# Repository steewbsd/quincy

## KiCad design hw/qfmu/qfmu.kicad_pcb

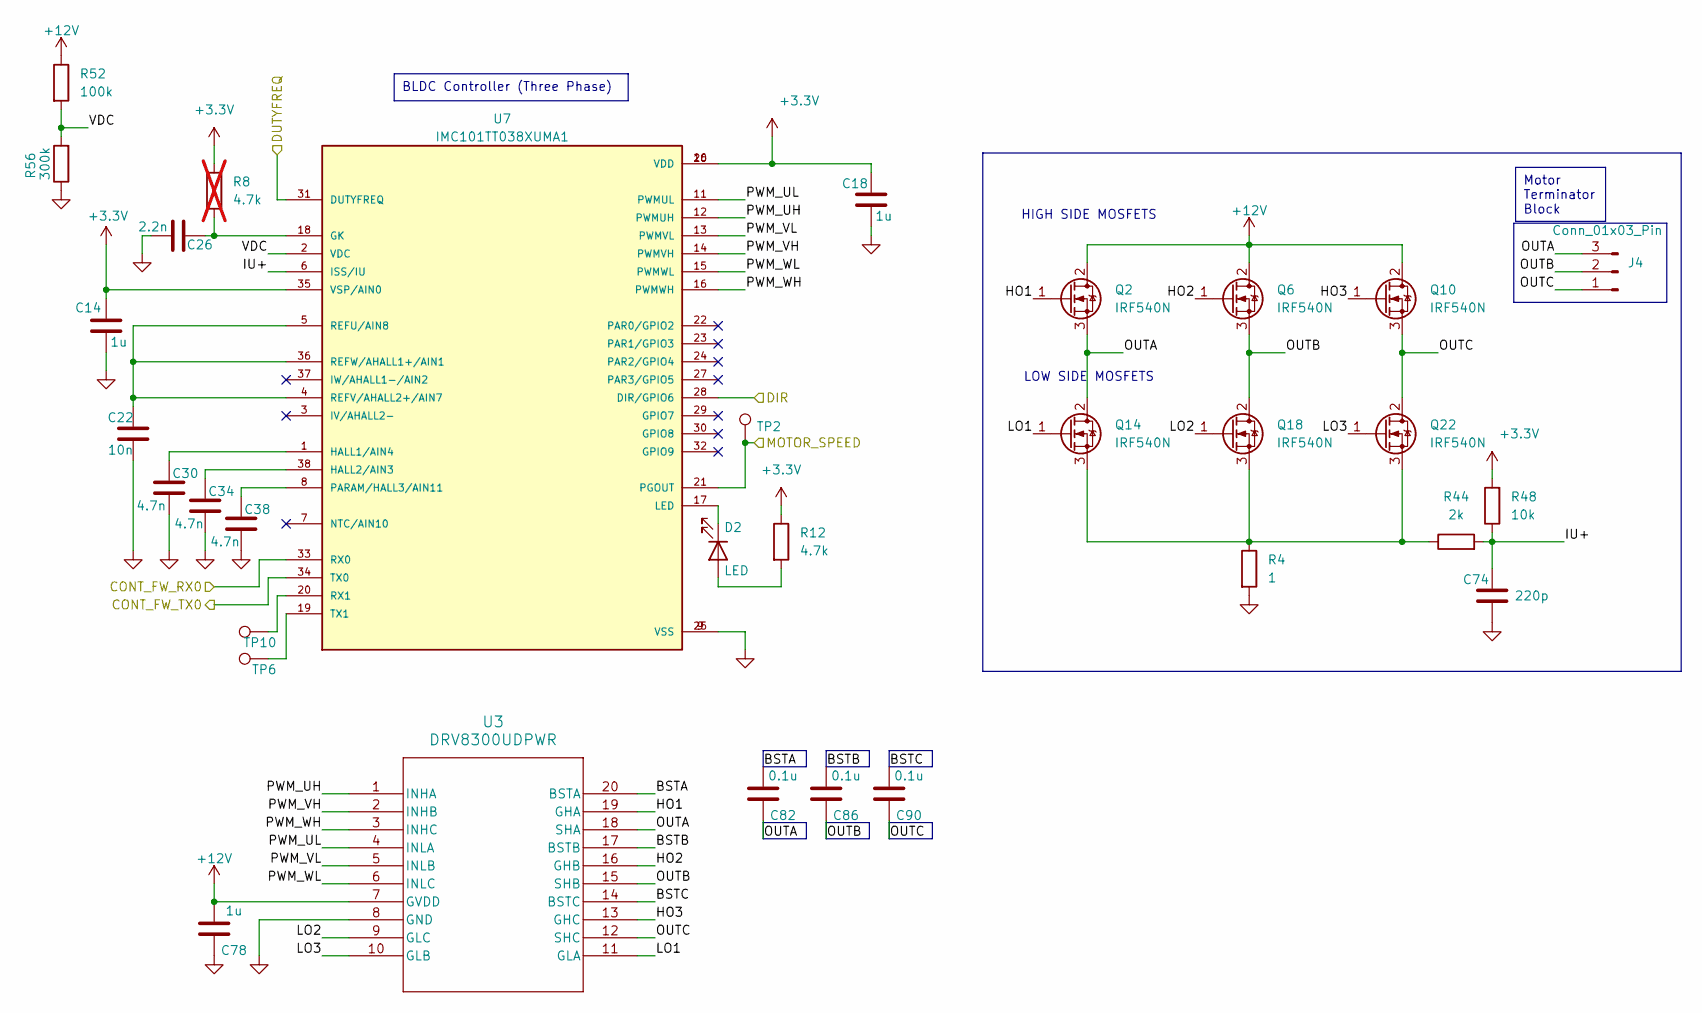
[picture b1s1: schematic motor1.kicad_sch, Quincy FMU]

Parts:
C14, C18, C78: 1u; C_0805_2012Metric_Pad1.18x1.45mm_HandSolder
C22: 10n; C_0805_2012Metric_Pad1.18x1.45mm_HandSolder
C26: 2.2n; C_0805_2012Metric_Pad1.18x1.45mm_HandSolder
C30, C34, C38: 4.7n; C_0805_2012Metric_Pad1.18x1.45mm_HandSolder
C74: 220p; C_0805_2012Metric_Pad1.18x1.45mm_HandSolder
C82, C86, C90: 0.1u; C_0805_2012Metric_Pad1.18x1.45mm_HandSolder
D2: LED; LED_1206_3216Metric_Pad1.42x1.75mm_HandSolder
J4: Conn_01x03_Pin; PhoenixContact_SPT_1.5_3-H-3.5_1x03_P3.5mm_Horizontal
Q2, Q6, Q10, Q14, Q18, Q22: IRF540N; TO-220-3_Horizontal_TabDown
R4: 1; R_0805_2012Metric_Pad1.20x1.40mm_HandSolder
R8: 4.7k; R_0805_2012Metric_Pad1.20x1.40mm_HandSolder; not fitted
R12: 4.7k; R_0805_2012Metric_Pad1.20x1.40mm_HandSolder
R44: 2k; R_0805_2012Metric_Pad1.20x1.40mm_HandSolder
R48: 10k; R_0805_2012Metric_Pad1.20x1.40mm_HandSolder
R52: 100k; R_0805_2012Metric_Pad1.20x1.40mm_HandSolder
R56: 300k; R_0805_2012Metric_Pad1.20x1.40mm_HandSolder
TP2, TP6, TP10: TestPoint; Pin_D0.7mm_L6.5mm_W1.8mm_FlatFork
U3: DRV8300UDPWR; TSSOP_0DIPWR_TEX
U7: IMC101TT038XUMA1; SOP50P640X110-38N; PARTREV 1.6

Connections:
+3.3V: C14.1, C18.1, R8.1, R12.1, R48.2, U7.10 (VDD), U7.26 (VDD), U7.35 (VSP/AIN0); also elsewhere on the board
+12V: C78.2, Q2.2 (D), Q6.2 (D), Q10.2 (D), R52.1, U3.7 (GVDD); also elsewhere on the board
/Microcontroller/CONT_FW_RX0_2: U7.33 (RX0); also elsewhere on the board
/Microcontroller/CONT_FW_TX0_2: U7.34 (TX0); also elsewhere on the board
/Microcontroller/DIR2: U7.28 (DIR/GPIO6); also elsewhere on the board
/Microcontroller/DUTY2: U7.31 (DUTYFREQ); also elsewhere on the board
/Microcontroller/MOTOR_SPEED2: TP2.1, U7.21 (PGOUT); also elsewhere on the board
/Motor 2/BSTA: C82.2, U3.20 (BSTA)
/Motor 2/BSTB: C86.2, U3.17 (BSTB)
/Motor 2/BSTC: C90.2, U3.14 (BSTC)
/Motor 2/HO1: Q2.1 (G), U3.19 (GHA)
/Motor 2/HO2: Q6.1 (G), U3.16 (GHB)
/Motor 2/HO3: Q10.1 (G), U3.13 (GHC)
/Motor 2/IU+: C74.1, R44.2, R48.1, U7.6 (ISS/IU)
/Motor 2/LO1: Q14.1 (G), U3.11 (GLA)
/Motor 2/LO2: Q18.1 (G), U3.9 (GLC)
/Motor 2/LO3: Q22.1 (G), U3.10 (GLB)
/Motor 2/OUTA: C82.1, J4.3, Q2.3 (S), Q14.2 (D), U3.18 (SHA)
/Motor 2/OUTB: C86.1, J4.2, Q6.3 (S), Q18.2 (D), U3.15 (SHB)
/Motor 2/OUTC: C90.1, J4.1, Q10.3 (S), Q22.2 (D), U3.12 (SHC)
/Motor 2/PWM_UH: U3.1 (INHA), U7.12 (PWMUH)
/Motor 2/PWM_UL: U3.4 (INLA), U7.11 (PWMUL)
/Motor 2/PWM_VH: U3.2 (INHB), U7.14 (PWMVH)
/Motor 2/PWM_VL: U3.5 (INLB), U7.13 (PWMVL)
/Motor 2/PWM_WH: U3.3 (INHC), U7.16 (PWMWH)
/Motor 2/PWM_WL: U3.6 (INLC), U7.15 (PWMWL)
/Motor 2/VDC: R52.2, R56.2, U7.2 (VDC)
GND: C14.2, C18.2, C22.2, C26.1, C30.2, C34.2, C38.2, C74.2, C78.1, R4.2, R56.1, U3.8 (GND), U7.9 (VSS), U7.25 (VSS); also elsewhere on the board
unnamed: D2.2 (A), R12.2
unnamed: D2.1 (K), U7.17 (LED)
unnamed: Q14.3 (S), Q18.3 (S), Q22.3 (S), R4.1, R44.1
unnamed: C26.2, R8.2, U7.18 (GK)
unnamed: C30.1, U7.1 (HALL1/AIN4)
unnamed: C34.1, U7.38 (HALL2/AIN3)
unnamed: C38.1, U7.8 (PARAM/HALL3/AIN11)
unnamed: C22.1, U7.4 (REFV/AHALL2+/AIN7), U7.5 (REFU/AIN8), U7.36 (REFW/AHALL1+/AIN1)
unnamed: TP10.1, U7.20 (RX1)
unnamed: TP6.1, U7.19 (TX1)

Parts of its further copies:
C13, C15, C16, C17, C19, C20, C77, C79, C80: 1u; C_0805_2012Metric_Pad1.18x1.45mm_HandSolder
C21, C23, C24: 10n; C_0805_2012Metric_Pad1.18x1.45mm_HandSolder
C25, C27, C28: 2.2n; C_0805_2012Metric_Pad1.18x1.45mm_HandSolder
C29, C31, C32, C33, C35, C36, C37, C39, C40: 4.7n; C_0805_2012Metric_Pad1.18x1.45mm_HandSolder
C73, C75, C76: 220p; C_0805_2012Metric_Pad1.18x1.45mm_HandSolder
C81, C83, C84, C85, C87, C88, C89, C91, C92: 0.1u; C_0805_2012Metric_Pad1.18x1.45mm_HandSolder
D1, D3, D4: LED; LED_1206_3216Metric_Pad1.42x1.75mm_HandSolder
J3, J5, J6: Conn_01x03_Pin; PhoenixContact_SPT_1.5_3-H-3.5_1x03_P3.5mm_Horizontal
Q1, Q3, Q4, Q5, Q7, Q8, Q9, Q11, Q12, Q13, Q15, Q16, Q17, Q19, Q20, Q21, Q23, Q24: IRF540N; TO-220-3_Horizontal_TabDown
R2, R41, R42: 1; R_0805_2012Metric_Pad1.20x1.40mm_HandSolder
R7, R9, R10: 4.7k; R_0805_2012Metric_Pad1.20x1.40mm_HandSolder; not fitted
R11, R13, R14: 4.7k; R_0805_2012Metric_Pad1.20x1.40mm_HandSolder
R43, R45, R46: 2k; R_0805_2012Metric_Pad1.20x1.40mm_HandSolder
R47, R49, R50: 10k; R_0805_2012Metric_Pad1.20x1.40mm_HandSolder
R51, R53, R54: 100k; R_0805_2012Metric_Pad1.20x1.40mm_HandSolder
R55, R57, R58: 300k; R_0805_2012Metric_Pad1.20x1.40mm_HandSolder
TP1, TP3, TP4, TP5, TP7, TP8, TP9, TP11, TP12: TestPoint; Pin_D0.7mm_L6.5mm_W1.8mm_FlatFork
U2, U4, U5: DRV8300UDPWR; TSSOP_0DIPWR_TEX
U6, U8, U9: IMC101TT038XUMA1; SOP50P640X110-38N; PARTREV 1.6

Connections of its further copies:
+3.3V: C13.1, C15.1, C16.1, C17.1, C19.1, C20.1, R7.1, R9.1, R10.1, R11.1, R13.1, R14.1, R47.2, R49.2, R50.2, U6.10 (VDD), U6.26 (VDD), U6.35 (VSP/AIN0), U8.10 (VDD), U8.26 (VDD), U8.35 (VSP/AIN0), U9.10 (VDD), U9.26 (VDD), U9.35 (VSP/AIN0); also elsewhere on the board
+12V: C77.2, C79.2, C80.2, Q1.2 (D), Q3.2 (D), Q4.2 (D), Q5.2 (D), Q7.2 (D), Q8.2 (D), Q9.2 (D), Q11.2 (D), Q12.2 (D), R51.1, R53.1, R54.1, U2.7 (GVDD), U4.7 (GVDD), U5.7 (GVDD); also elsewhere on the board
/Microcontroller/CONT_FW_RX0_1: U6.33 (RX0); also elsewhere on the board
/Microcontroller/CONT_FW_RX0_3: U8.33 (RX0); also elsewhere on the board
/Microcontroller/CONT_FW_RX0_4: U9.33 (RX0); also elsewhere on the board
/Microcontroller/CONT_FW_TX0_1: U6.34 (TX0); also elsewhere on the board
/Microcontroller/CONT_FW_TX0_3: U8.34 (TX0); also elsewhere on the board
/Microcontroller/CONT_FW_TX0_4: U9.34 (TX0); also elsewhere on the board
/Microcontroller/DIR1: U6.28 (DIR/GPIO6); also elsewhere on the board
/Microcontroller/DIR3: U8.28 (DIR/GPIO6); also elsewhere on the board
/Microcontroller/DIR4: U9.28 (DIR/GPIO6); also elsewhere on the board
/Microcontroller/DUTY1: U6.31 (DUTYFREQ); also elsewhere on the board
/Microcontroller/DUTY3: U8.31 (DUTYFREQ); also elsewhere on the board
/Microcontroller/DUTY4: U9.31 (DUTYFREQ); also elsewhere on the board
/Microcontroller/MOTOR_SPEED1: TP1.1, U6.21 (PGOUT); also elsewhere on the board
/Microcontroller/MOTOR_SPEED3: TP3.1, U8.21 (PGOUT); also elsewhere on the board
/Microcontroller/MOTOR_SPEED4: TP4.1, U9.21 (PGOUT); also elsewhere on the board
/Motor 1/BSTA: C81.2, U2.20 (BSTA)
/Motor 1/BSTB: C85.2, U2.17 (BSTB)
/Motor 1/BSTC: C89.2, U2.14 (BSTC)
/Motor 1/HO1: Q1.1 (G), U2.19 (GHA)
/Motor 1/HO2: Q5.1 (G), U2.16 (GHB)
/Motor 1/HO3: Q9.1 (G), U2.13 (GHC)
/Motor 1/IU+: C73.1, R43.2, R47.1, U6.6 (ISS/IU)
/Motor 1/LO1: Q13.1 (G), U2.11 (GLA)
/Motor 1/LO2: Q17.1 (G), U2.9 (GLC)
/Motor 1/LO3: Q21.1 (G), U2.10 (GLB)
/Motor 1/OUTA: C81.1, J3.3, Q1.3 (S), Q13.2 (D), U2.18 (SHA)
/Motor 1/OUTB: C85.1, J3.2, Q5.3 (S), Q17.2 (D), U2.15 (SHB)
/Motor 1/OUTC: C89.1, J3.1, Q9.3 (S), Q21.2 (D), U2.12 (SHC)
/Motor 1/PWM_UH: U2.1 (INHA), U6.12 (PWMUH)
/Motor 1/PWM_UL: U2.4 (INLA), U6.11 (PWMUL)
/Motor 1/PWM_VH: U2.2 (INHB), U6.14 (PWMVH)
/Motor 1/PWM_VL: U2.5 (INLB), U6.13 (PWMVL)
/Motor 1/PWM_WH: U2.3 (INHC), U6.16 (PWMWH)
/Motor 1/PWM_WL: U2.6 (INLC), U6.15 (PWMWL)
/Motor 1/VDC: R51.2, R55.2, U6.2 (VDC)
/Motor 3/BSTA: C83.2, U4.20 (BSTA)
/Motor 3/BSTB: C87.2, U4.17 (BSTB)
/Motor 3/BSTC: C91.2, U4.14 (BSTC)
/Motor 3/HO1: Q3.1 (G), U4.19 (GHA)
/Motor 3/HO2: Q7.1 (G), U4.16 (GHB)
/Motor 3/HO3: Q11.1 (G), U4.13 (GHC)
/Motor 3/IU+: C75.1, R45.2, R49.1, U8.6 (ISS/IU)
/Motor 3/LO1: Q15.1 (G), U4.11 (GLA)
/Motor 3/LO2: Q19.1 (G), U4.9 (GLC)
/Motor 3/LO3: Q23.1 (G), U4.10 (GLB)
/Motor 3/OUTA: C83.1, J5.3, Q3.3 (S), Q15.2 (D), U4.18 (SHA)
/Motor 3/OUTB: C87.1, J5.2, Q7.3 (S), Q19.2 (D), U4.15 (SHB)
/Motor 3/OUTC: C91.1, J5.1, Q11.3 (S), Q23.2 (D), U4.12 (SHC)
/Motor 3/PWM_UH: U4.1 (INHA), U8.12 (PWMUH)
/Motor 3/PWM_UL: U4.4 (INLA), U8.11 (PWMUL)
/Motor 3/PWM_VH: U4.2 (INHB), U8.14 (PWMVH)
/Motor 3/PWM_VL: U4.5 (INLB), U8.13 (PWMVL)
/Motor 3/PWM_WH: U4.3 (INHC), U8.16 (PWMWH)
/Motor 3/PWM_WL: U4.6 (INLC), U8.15 (PWMWL)
/Motor 3/VDC: R53.2, R57.2, U8.2 (VDC)
/Motor 4/BSTA: C84.2, U5.20 (BSTA)
/Motor 4/BSTB: C88.2, U5.17 (BSTB)
/Motor 4/BSTC: C92.2, U5.14 (BSTC)
/Motor 4/HO1: Q4.1 (G), U5.19 (GHA)
/Motor 4/HO2: Q8.1 (G), U5.16 (GHB)
/Motor 4/HO3: Q12.1 (G), U5.13 (GHC)
/Motor 4/IU+: C76.1, R46.2, R50.1, U9.6 (ISS/IU)
/Motor 4/LO1: Q16.1 (G), U5.11 (GLA)
/Motor 4/LO2: Q20.1 (G), U5.9 (GLC)
/Motor 4/LO3: Q24.1 (G), U5.10 (GLB)
/Motor 4/OUTA: C84.1, J6.3, Q4.3 (S), Q16.2 (D), U5.18 (SHA)
/Motor 4/OUTB: C88.1, J6.2, Q8.3 (S), Q20.2 (D), U5.15 (SHB)
/Motor 4/OUTC: C92.1, J6.1, Q12.3 (S), Q24.2 (D), U5.12 (SHC)
/Motor 4/PWM_UH: U5.1 (INHA), U9.12 (PWMUH)
/Motor 4/PWM_UL: U5.4 (INLA), U9.11 (PWMUL)
/Motor 4/PWM_VH: U5.2 (INHB), U9.14 (PWMVH)
/Motor 4/PWM_VL: U5.5 (INLB), U9.13 (PWMVL)
/Motor 4/PWM_WH: U5.3 (INHC), U9.16 (PWMWH)
/Motor 4/PWM_WL: U5.6 (INLC), U9.15 (PWMWL)
/Motor 4/VDC: R54.2, R58.2, U9.2 (VDC)
GND: C13.2, C15.2, C16.2, C17.2, C19.2, C20.2, C21.2, C23.2, C24.2, C25.1, C27.1, C28.1, C29.2, C31.2, C32.2, C33.2, C35.2, C36.2, C37.2, C39.2, C40.2, C73.2, C75.2, C76.2, C77.1, C79.1, C80.1, R2.2, R41.2, R42.2, R55.1, R57.1, R58.1, U2.8 (GND), U4.8 (GND), U5.8 (GND), U6.9 (VSS), U6.25 (VSS), U8.9 (VSS), U8.25 (VSS), U9.9 (VSS), U9.25 (VSS); also elsewhere on the board
unnamed: D1.2 (A), R11.2
unnamed: D1.1 (K), U6.17 (LED)
unnamed: D3.2 (A), R13.2
unnamed: D3.1 (K), U8.17 (LED)
unnamed: D4.2 (A), R14.2
unnamed: D4.1 (K), U9.17 (LED)
unnamed: Q13.3 (S), Q17.3 (S), Q21.3 (S), R2.1, R43.1
unnamed: Q15.3 (S), Q19.3 (S), Q23.3 (S), R41.1, R45.1
unnamed: Q16.3 (S), Q20.3 (S), Q24.3 (S), R42.1, R46.1
unnamed: C25.2, R7.2, U6.18 (GK)
unnamed: C29.1, U6.1 (HALL1/AIN4)
unnamed: C33.1, U6.38 (HALL2/AIN3)
unnamed: C37.1, U6.8 (PARAM/HALL3/AIN11)
unnamed: C21.1, U6.4 (REFV/AHALL2+/AIN7), U6.5 (REFU/AIN8), U6.36 (REFW/AHALL1+/AIN1)
unnamed: TP9.1, U6.20 (RX1)
unnamed: TP5.1, U6.19 (TX1)
unnamed: C27.2, R9.2, U8.18 (GK)
unnamed: C31.1, U8.1 (HALL1/AIN4)
unnamed: C35.1, U8.38 (HALL2/AIN3)
unnamed: C39.1, U8.8 (PARAM/HALL3/AIN11)
unnamed: C23.1, U8.4 (REFV/AHALL2+/AIN7), U8.5 (REFU/AIN8), U8.36 (REFW/AHALL1+/AIN1)
unnamed: TP11.1, U8.20 (RX1)
unnamed: TP7.1, U8.19 (TX1)
unnamed: C28.2, R10.2, U9.18 (GK)
unnamed: C32.1, U9.1 (HALL1/AIN4)
unnamed: C36.1, U9.38 (HALL2/AIN3)
unnamed: C40.1, U9.8 (PARAM/HALL3/AIN11)
unnamed: C24.1, U9.4 (REFV/AHALL2+/AIN7), U9.5 (REFU/AIN8), U9.36 (REFW/AHALL1+/AIN1)
unnamed: TP12.1, U9.20 (RX1)
unnamed: TP8.1, U9.19 (TX1)

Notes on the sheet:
Motor Terminator Block
BLDC Controller (Three Phase)
HIGH SIDE MOSFETS
LOW SIDE MOSFETS

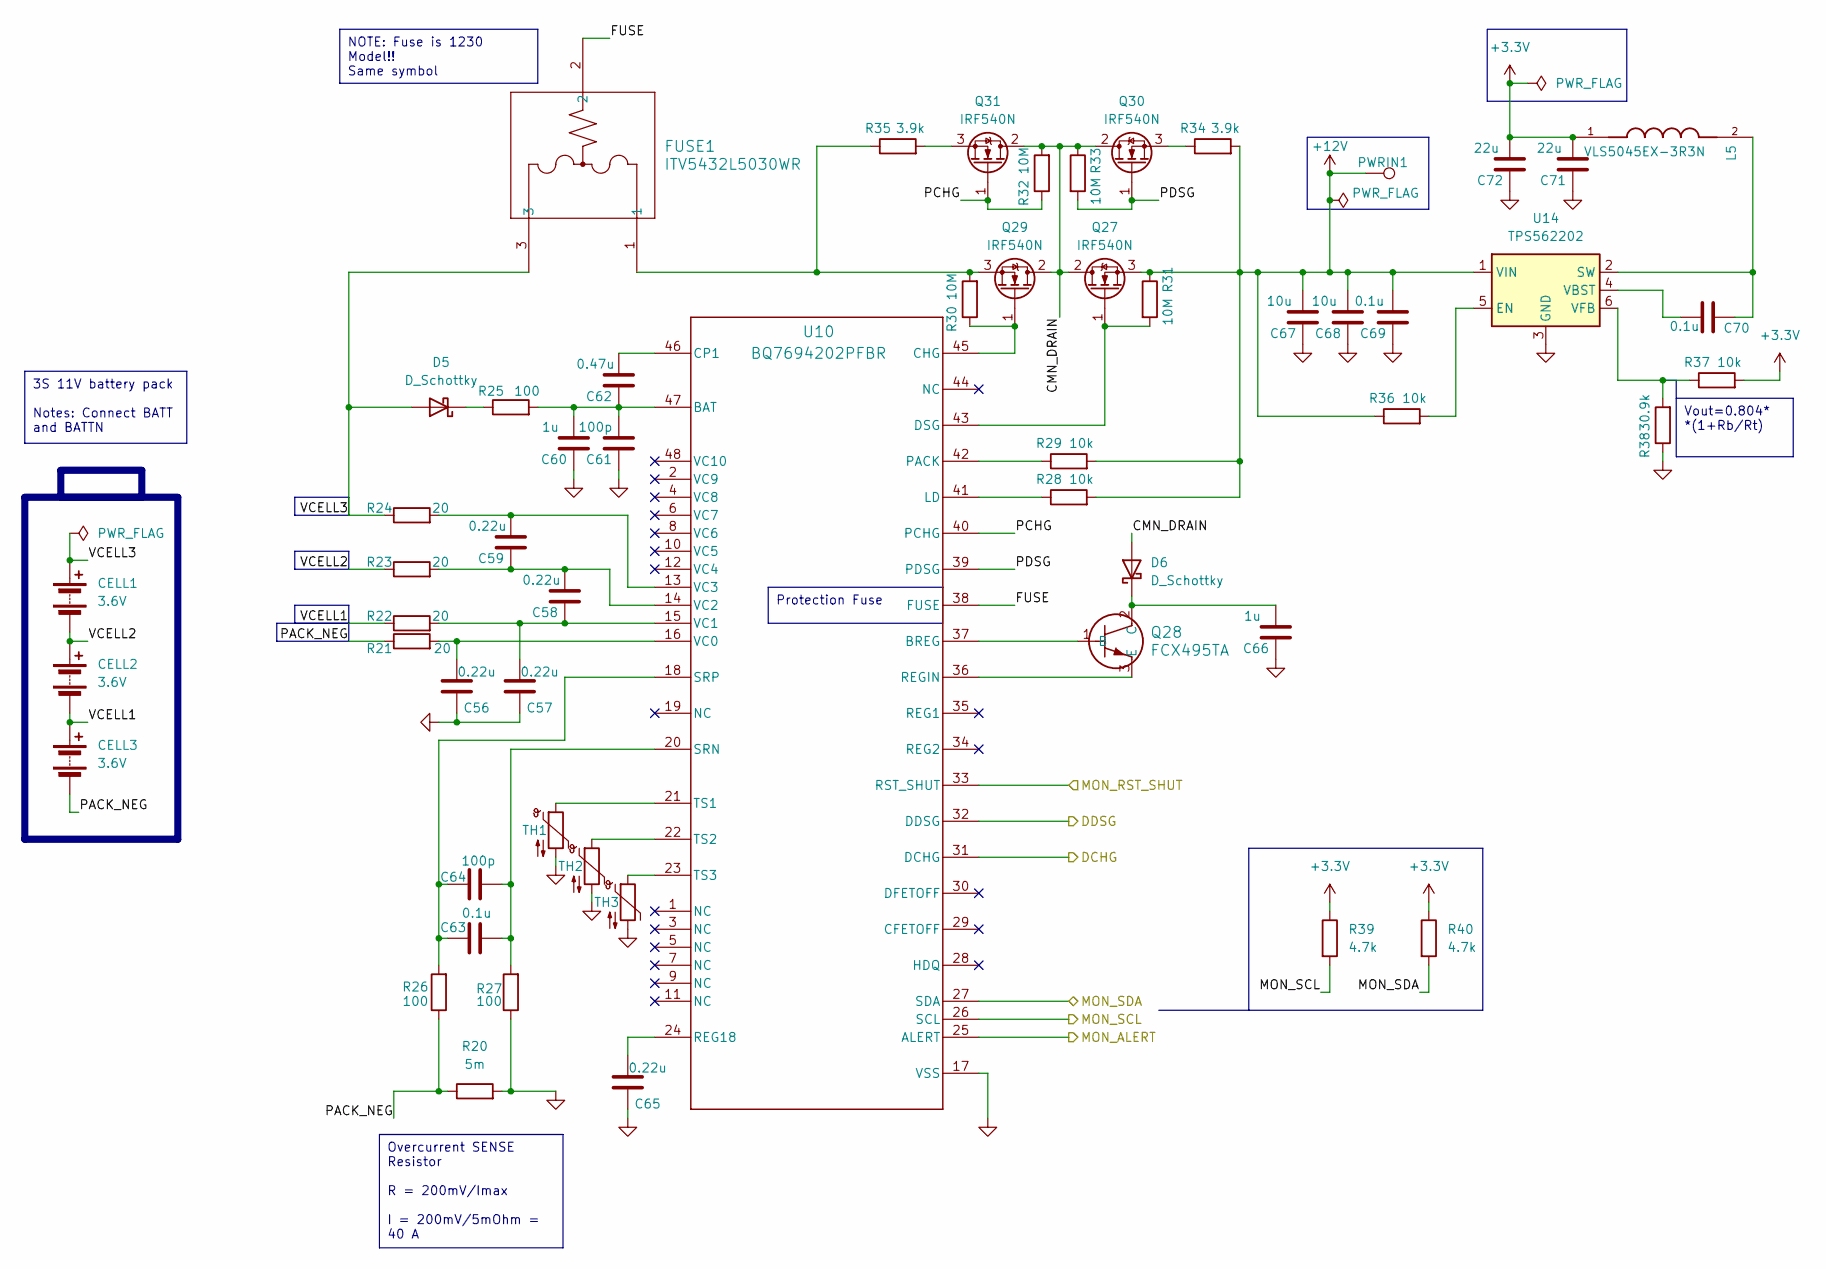
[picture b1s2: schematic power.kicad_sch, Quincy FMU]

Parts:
C56, C57, C58, C59, C65: 0.22u; C_0805_2012Metric_Pad1.18x1.45mm_HandSolder
C60, C66: 1u; C_0805_2012Metric_Pad1.18x1.45mm_HandSolder
C61, C64: 100p; C_0805_2012Metric_Pad1.18x1.45mm_HandSolder
C62: 0.47u; C_0805_2012Metric_Pad1.18x1.45mm_HandSolder
C63, C69, C70: 0.1u; C_0805_2012Metric_Pad1.18x1.45mm_HandSolder
C67, C68: 10u; C_0805_2012Metric_Pad1.18x1.45mm_HandSolder
C71, C72: 22u; C_0805_2012Metric_Pad1.18x1.45mm_HandSolder
CELL1, CELL2, CELL3: 3.6V
D5, D6: D_Schottky; D_SOD-123
FUSE1: ITV5432L5030WR; QFN4_ITV5432_LTF
L5: VLS5045EX-3R3N; IND_VLS5045EX-3R3N; PARTREV N/A
PWRIN1: TestPoint; Pin_D0.7mm_L6.5mm_W1.8mm_FlatFork
Q27, Q29, Q30, Q31: IRF540N; TO-220-3_Horizontal_TabDown
Q28: FCX495TA; SOT89_DIO
R20: 5m; R_2512_6332Metric_Pad1.40x3.35mm_HandSolder
R21, R22, R23, R24: 20; R_0805_2012Metric_Pad1.20x1.40mm_HandSolder
R25, R26, R27: 100; R_0805_2012Metric_Pad1.20x1.40mm_HandSolder
R28, R29, R36, R37: 10k; R_0805_2012Metric_Pad1.20x1.40mm_HandSolder
R30, R31, R32, R33: 10M; R_0805_2012Metric_Pad1.20x1.40mm_HandSolder
R34, R35: 3.9k; R_0805_2012Metric_Pad1.20x1.40mm_HandSolder
R38: 30.9k; R_0805_2012Metric_Pad1.20x1.40mm_HandSolder
R39, R40: 4.7k; R_0805_2012Metric_Pad1.20x1.40mm_HandSolder
TH1, TH2, TH3: Thermistor_NTC; R_0603_1608Metric_Pad0.98x0.95mm_HandSolder
U10: BQ7694202PFBR; PFB0048A_N
U14: TPS562202; SOT-563

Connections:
+3.3V: C71.2, C72.2, L5.1, R37.2, R39.1, R40.1; also elsewhere on the board
+12V: C67.2, C68.2, C69.2, PWRIN1.1, Q27.3 (S), R28.2, R29.2, R31.1, R34.2, R36.1, U14.1 (VIN); also elsewhere on the board
/Microcontroller/DCHG: U10.31 (DCHG); also elsewhere on the board
/Microcontroller/DDSG: U10.32 (DDSG); also elsewhere on the board
/Microcontroller/MON_ALERT: U10.25 (ALERT); also elsewhere on the board
/Microcontroller/MON_RST_SHUT: U10.33 (RST_SHUT); also elsewhere on the board
/Power/CMN_DRAIN: D6.2 (A), Q27.2 (D), Q29.2 (D), Q30.2 (D), Q31.2 (D), R32.2, R33.1
/Power/FUSE: FUSE1.2, U10.38 (FUSE)
/Power/MON_SCL: R39.2, U10.26 (SCL); also elsewhere on the board
/Power/MON_SDA: R40.2, U10.27 (SDA); also elsewhere on the board
/Power/PACK_NEG: CELL3.2 (-), R20.1, R21.1, R26.1
/Power/PCHG: Q31.1 (G), R32.1, U10.40 (PCHG)
/Power/PDSG: Q30.1 (G), R33.2, U10.39 (PDSG)
/Power/VCELL1: CELL2.2 (-), CELL3.1 (+), R22.1
/Power/VCELL2: CELL1.2 (-), CELL2.1 (+), R23.1
/Power/VCELL3: CELL1.1 (+), D5.2 (A), FUSE1.3, R24.1
GND: C56.1, C57.1, C60.1, C61.1, C65.1, C66.1, C67.1, C68.1, C69.1, C71.1, C72.1, R20.2, R27.1, R38.1, TH1.2, TH2.2, TH3.2, U10.17 (VSS), U14.3 (GND); also elsewhere on the board
unnamed: D5.1 (K), R25.1
unnamed: C66.2, D6.1 (K), Q28.2 (C)
unnamed: Q27.1 (G), R31.2, U10.43 (DSG)
unnamed: Q28.1 (B), U10.37 (BREG)
unnamed: Q28.3 (E), U10.36 (REGIN)
unnamed: Q29.1 (G), R30.1, U10.45 (CHG)
unnamed: FUSE1.1, Q29.3 (S), R30.2, R35.1
unnamed: Q30.3 (S), R34.1
unnamed: Q31.3 (S), R35.2
unnamed: C60.2, C61.2, C62.1, R25.2, U10.47 (BAT)
unnamed: C62.2, U10.46 (CP1)
unnamed: R28.1, U10.41 (LD)
unnamed: R29.1, U10.42 (PACK)
unnamed: C65.2, U10.24 (REG18)
unnamed: C63.1, C64.1, R27.2, U10.20 (SRN)
unnamed: C63.2, C64.2, R26.2, U10.18 (SRP)
unnamed: TH1.1, U10.21 (TS1)
unnamed: TH2.1, U10.22 (TS2)
unnamed: TH3.1, U10.23 (TS3)
unnamed: C56.2, R21.2, U10.16 (VC0)
unnamed: C57.2, C58.1, R22.2, U10.15 (VC1)
unnamed: C58.2, C59.1, R23.2, U10.14 (VC2)
unnamed: C59.2, R24.2, U10.13 (VC3)
unnamed: R36.2, U14.5 (EN)
unnamed: C70.1, L5.2, U14.2 (SW)
unnamed: C70.2, U14.4 (VBST)
unnamed: R37.1, R38.2, U14.6 (VFB)

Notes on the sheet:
NOTE: Fuse is 1230 Model!! Same symbol
Vout=0.804* *(1+Rb/Rt)
Protection Fuse
Overcurrent SENSE Resistor R = 200mV/Imax I = 200mV/5mOhm = 40 A
3S 11V battery pack Notes: Connect BATT and BATTN

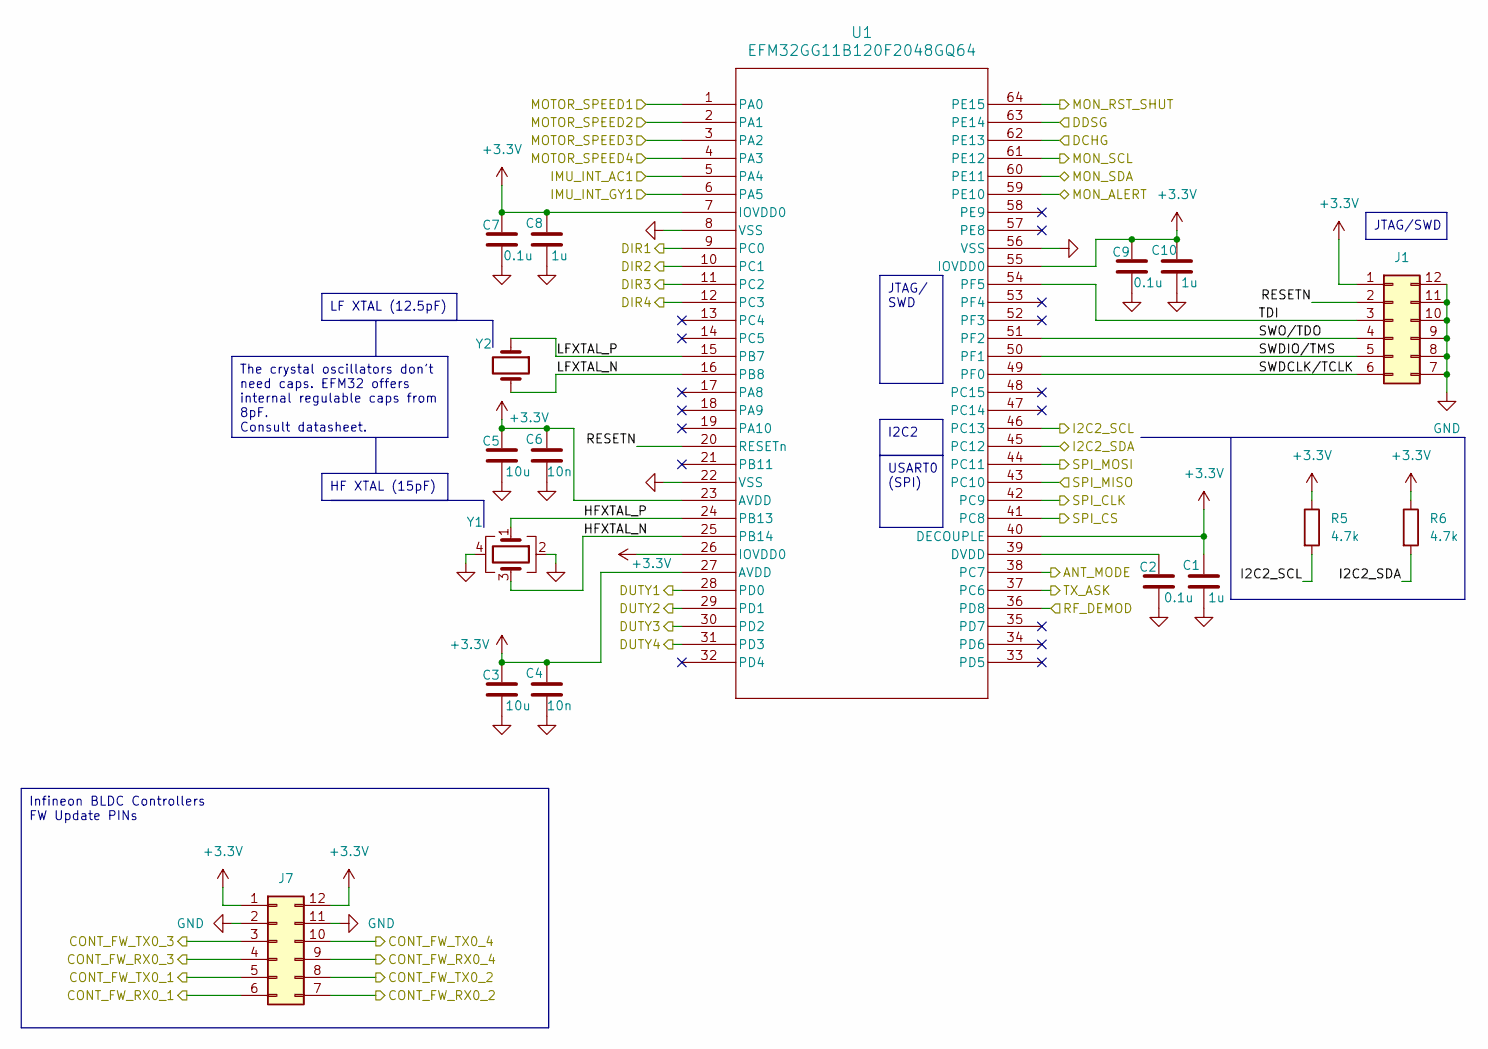
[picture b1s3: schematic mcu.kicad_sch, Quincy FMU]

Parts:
C1, C8, C10: 1u; C_0805_2012Metric_Pad1.18x1.45mm_HandSolder
C2, C7, C9: 0.1u; C_0805_2012Metric_Pad1.18x1.45mm_HandSolder
C3, C5: 10u; C_0805_2012Metric_Pad1.18x1.45mm_HandSolder
C4, C6: 10n; C_0805_2012Metric_Pad1.18x1.45mm_HandSolder
J1, J7: Conn_02x06_Counter_Clockwise; PinHeader_2x06_P2.54mm_Vertical
R5, R6: 4.7k; R_0805_2012Metric_Pad1.20x1.40mm_HandSolder
U1: EFM32GG11B120F2048GQ64; TQFP64_10X10_SIL
Y1: Crystal_GND24; Crystal_SMD_3225-4Pin_3.2x2.5mm_HandSoldering
Y2: Crystal; Crystal_SMD_EuroQuartz_EQ161-2Pin_3.2x1.5mm_HandSoldering

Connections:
+3.3V: C1.1, C3.1, C4.1, C5.1, C6.1, C7.1, C8.1, C9.1, C10.1, J1.1, J7.1, J7.12, R5.1, R6.1, U1.7 (IOVDD0), U1.23 (AVDD), U1.26 (IOVDD0), U1.27 (AVDD), U1.40 (DECOUPLE), U1.55 (IOVDD0); also elsewhere on the board
/Microcontroller/ANT_MODE: U1.38 (PC7); also elsewhere on the board
/Microcontroller/CONT_FW_RX0_1: J7.6; also elsewhere on the board
/Microcontroller/CONT_FW_RX0_2: J7.7; also elsewhere on the board
/Microcontroller/CONT_FW_RX0_3: J7.4; also elsewhere on the board
/Microcontroller/CONT_FW_RX0_4: J7.9; also elsewhere on the board
/Microcontroller/CONT_FW_TX0_1: J7.5; also elsewhere on the board
/Microcontroller/CONT_FW_TX0_2: J7.8; also elsewhere on the board
/Microcontroller/CONT_FW_TX0_3: J7.3; also elsewhere on the board
/Microcontroller/CONT_FW_TX0_4: J7.10; also elsewhere on the board
/Microcontroller/DCHG: U1.62 (PE13); also elsewhere on the board
/Microcontroller/DDSG: U1.63 (PE14); also elsewhere on the board
/Microcontroller/DIR1: U1.9 (PC0); also elsewhere on the board
/Microcontroller/DIR2: U1.10 (PC1); also elsewhere on the board
/Microcontroller/DIR3: U1.11 (PC2); also elsewhere on the board
/Microcontroller/DIR4: U1.12 (PC3); also elsewhere on the board
/Microcontroller/DUTY1: U1.28 (PD0); also elsewhere on the board
/Microcontroller/DUTY2: U1.29 (PD1); also elsewhere on the board
/Microcontroller/DUTY3: U1.30 (PD2); also elsewhere on the board
/Microcontroller/DUTY4: U1.31 (PD3); also elsewhere on the board
/Microcontroller/HFXTAL_N: U1.25 (PB14), Y1.3
/Microcontroller/HFXTAL_P: U1.24 (PB13), Y1.1
/Microcontroller/I2C2_SCL: R5.2, U1.46 (PC13); also elsewhere on the board
/Microcontroller/I2C2_SDA: R6.2, U1.45 (PC12); also elsewhere on the board
/Microcontroller/IMU_INT_AC1: U1.5 (PA4); also elsewhere on the board
/Microcontroller/IMU_INT_GY1: U1.6 (PA5); also elsewhere on the board
/Microcontroller/LFXTAL_N: U1.16 (PB8), Y2.2
/Microcontroller/LFXTAL_P: U1.15 (PB7), Y2.1
/Microcontroller/MON_ALERT: U1.59 (PE10); also elsewhere on the board
/Microcontroller/MON_RST_SHUT: U1.64 (PE15); also elsewhere on the board
/Microcontroller/MOTOR_SPEED1: U1.1 (PA0); also elsewhere on the board
/Microcontroller/MOTOR_SPEED2: U1.2 (PA1); also elsewhere on the board
/Microcontroller/MOTOR_SPEED3: U1.3 (PA2); also elsewhere on the board
/Microcontroller/MOTOR_SPEED4: U1.4 (PA3); also elsewhere on the board
/Microcontroller/RESETN: J1.2, U1.20 (RESETn)
/Microcontroller/RF_DEMOD: U1.36 (PD8); also elsewhere on the board
/Microcontroller/SPI_CLK: U1.42 (PC9)
/Microcontroller/SPI_CS: U1.41 (PC8)
/Microcontroller/SPI_MISO: U1.43 (PC10)
/Microcontroller/SPI_MOSI: U1.44 (PC11)
/Microcontroller/SWDCLK/TCLK: J1.6, U1.49 (PF0)
/Microcontroller/SWDIO/TMS: J1.5, U1.50 (PF1)
/Microcontroller/SWO/TDO: J1.4, U1.51 (PF2)
/Microcontroller/TDI: J1.3, U1.54 (PF5)
/Microcontroller/TX_ASK: U1.37 (PC6); also elsewhere on the board
/Power/MON_SCL: U1.61 (PE12); also elsewhere on the board
/Power/MON_SDA: U1.60 (PE11); also elsewhere on the board
GND: C1.2, C2.2, C3.2, C4.2, C5.2, C6.2, C7.2, C8.2, C9.2, C10.2, J1.7, J1.8, J1.9, J1.10, J1.11, J1.12, J7.2, J7.11, U1.8 (VSS), U1.22 (VSS), U1.56 (VSS), Y1.2, Y1.4; also elsewhere on the board
unnamed: C2.1, U1.39 (DVDD)

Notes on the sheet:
JTAG/ SWD
JTAG/SWD
The crystal oscillators don't need caps. EFM32 offers internal regulable caps from 8pF. Consult datasheet.
HF XTAL (15pF)
Infineon BLDC Controllers FW Update PINs
I2C2
USART0 (SPI)
LF XTAL (12.5pF)

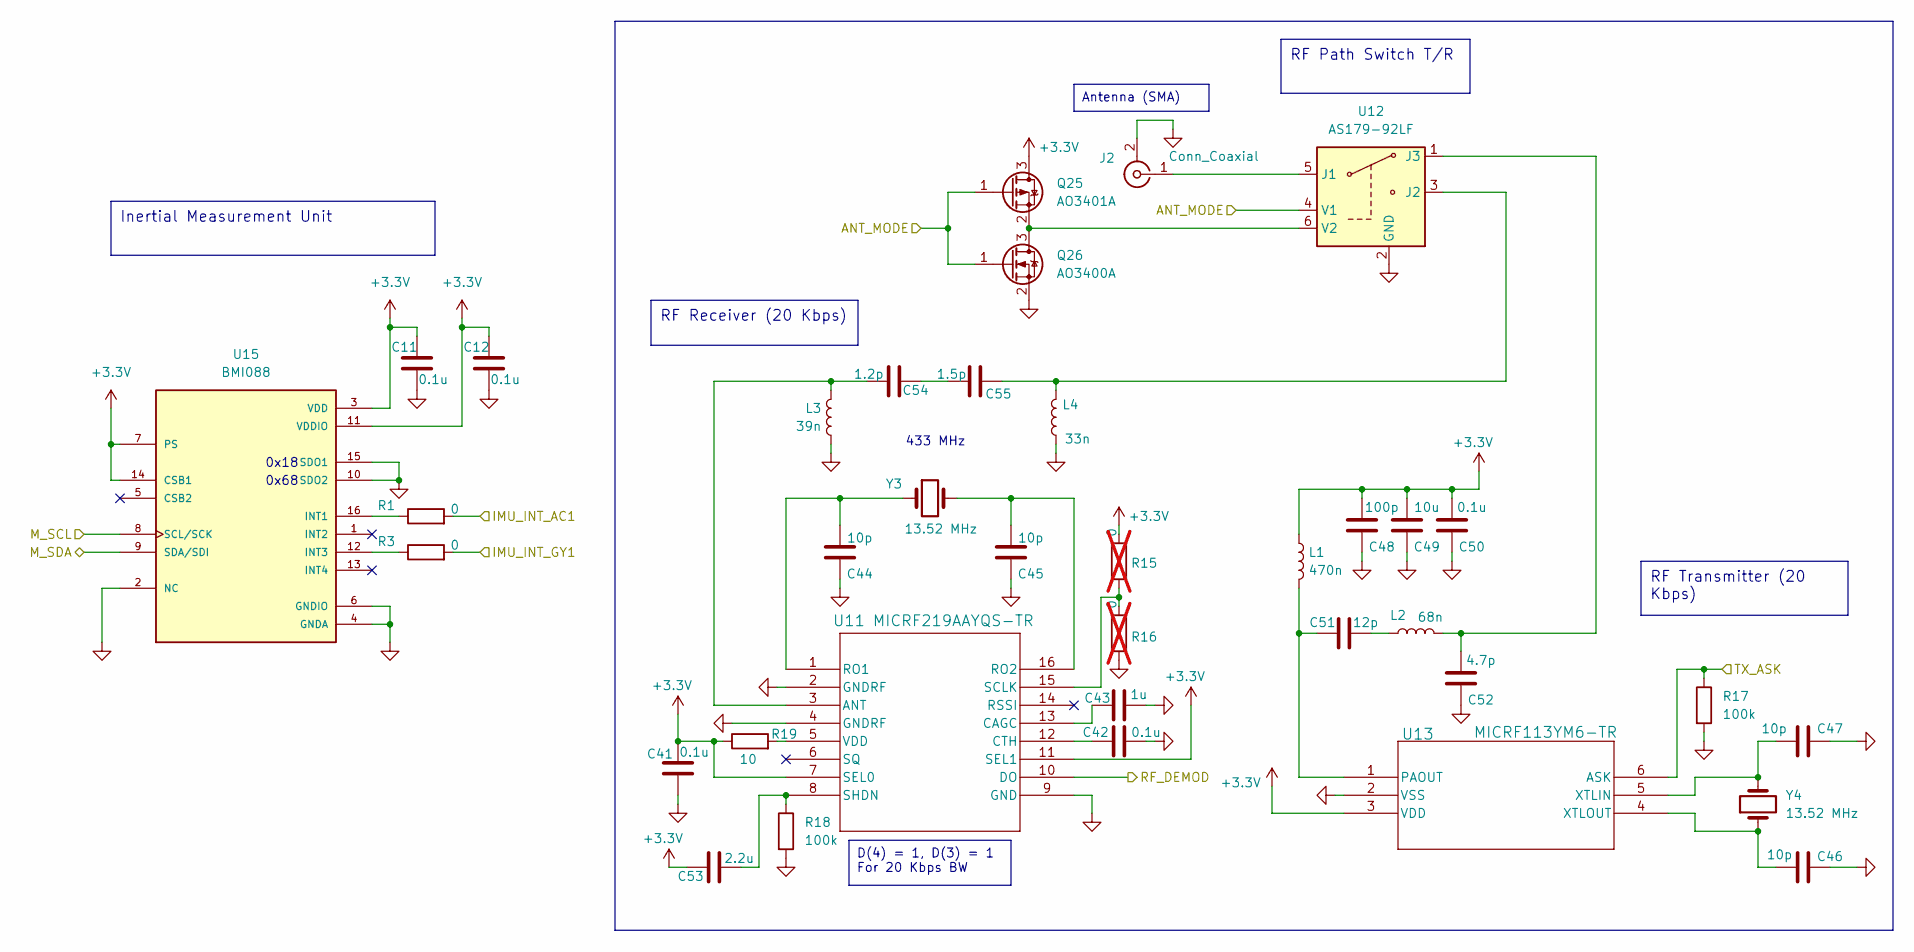
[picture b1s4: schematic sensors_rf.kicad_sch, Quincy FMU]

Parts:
C11, C12, C41, C42, C50: 0.1u; C_0805_2012Metric_Pad1.18x1.45mm_HandSolder
C43: 1u; C_0805_2012Metric_Pad1.18x1.45mm_HandSolder
C44, C45, C46, C47: 10p; C_0805_2012Metric_Pad1.18x1.45mm_HandSolder
C48: 100p; C_0805_2012Metric_Pad1.18x1.45mm_HandSolder
C49: 10u; C_0805_2012Metric_Pad1.18x1.45mm_HandSolder
C51: 12p; C_0603_1608Metric_Pad1.08x0.95mm_HandSolder
C52: 4.7p; C_0603_1608Metric_Pad1.08x0.95mm_HandSolder
C53: 2.2u; C_0805_2012Metric_Pad1.18x1.45mm_HandSolder
C54: 1.2p; C_0603_1608Metric_Pad1.08x0.95mm_HandSolder
C55: 1.5p; C_0603_1608Metric_Pad1.08x0.95mm_HandSolder
J2: Conn_Coaxial; SMA_Amphenol_901-144_Vertical
L1: 470n; L_0402_1005Metric_Pad0.77x0.64mm_HandSolder
L2: 68n; L_0603_1608Metric_Pad1.05x0.95mm_HandSolder
L3: 39n; L_0402_1005Metric_Pad0.77x0.64mm_HandSolder
L4: 33n; L_0603_1608Metric_Pad1.05x0.95mm_HandSolder
Q25: AO3401A; SOT-23
Q26: AO3400A; SOT-23
R1, R3: 0; R_0805_2012Metric_Pad1.20x1.40mm_HandSolder
R15, R16: 0; R_0805_2012Metric_Pad1.20x1.40mm_HandSolder; not fitted
R17, R18: 100k; R_0805_2012Metric_Pad1.20x1.40mm_HandSolder
R19: 10; R_0805_2012Metric_Pad1.20x1.40mm_HandSolder
U11: MICRF219AAYQS-TR; QSOP16_MC_MCH
U12: AS179-92LF; SOT-363_SC-70-6
U13: MICRF113YM6-TR; SOT-23-6_MC_MCH
U15: BMI088; PQFN50P450X300X100-16N
Y3, Y4: 13.52 MHz; Crystal_HC49-U_Horizontal

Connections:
+3.3V: C11.1, C12.1, C41.1, C48.2, C49.2, C50.2, C53.1, L1.1, Q25.3 (D), R15.2, R19.1, U11.7 (SEL0), U11.11 (SEL1), U13.3 (VDD), U15.3 (VDD), U15.7 (PS), U15.11 (VDDIO), U15.14 (CSB1); also elsewhere on the board
/Microcontroller/ANT_MODE: Q25.1 (G), Q26.1 (G), U12.4 (V1); also elsewhere on the board
/Microcontroller/I2C2_SCL: U15.8 (SCL/SCK); also elsewhere on the board
/Microcontroller/I2C2_SDA: U15.9 (SDA/SDI); also elsewhere on the board
/Microcontroller/IMU_INT_AC1: R1.2; also elsewhere on the board
/Microcontroller/IMU_INT_GY1: R3.2; also elsewhere on the board
/Microcontroller/RF_DEMOD: U11.10 (DO); also elsewhere on the board
/Microcontroller/TX_ASK: R17.1, U13.6 (ASK); also elsewhere on the board
GND: C11.2, C12.2, C41.2, C42.2, C43.2, C44.1, C45.1, C46.1, C47.1, C48.1, C49.1, C50.1, C52.1, J2.2 (Ext), L3.2, L4.2, Q26.2 (S), R16.1, R17.2, R18.2, U11.2 (GNDRF), U11.4 (GNDRF), U11.9 (GND), U12.2 (GND), U13.2 (VSS), U15.2 (NC), U15.4 (GNDA), U15.6 (GNDIO), U15.10 (SDO2), U15.15 (SDO1); also elsewhere on the board
unnamed: C51.2, L2.1
unnamed: C54.1, C55.2
unnamed: J2.1 (In), U12.5 (J1)
unnamed: Q25.2 (S), Q26.3 (D), U12.6 (V2)
unnamed: C54.2, L3.1, U11.3 (ANT)
unnamed: C43.1, U11.13 (CAGC)
unnamed: C42.1, U11.12 (CTH)
unnamed: C44.2, U11.1 (RO1), Y3.1
unnamed: C45.2, U11.16 (RO2), Y3.2
unnamed: R15.1, R16.2, U11.15 (SCLK)
unnamed: C53.2, R18.1, U11.8 (SHDN)
unnamed: R19.2, U11.5 (VDD)
unnamed: C55.1, L4.1, U12.3 (J2)
unnamed: C52.2, L2.2, U12.1 (J3)
unnamed: C51.1, L1.2, U13.1 (PAOUT)
unnamed: C47.2, U13.5 (XTLIN), Y4.2
unnamed: C46.2, U13.4 (XTLOUT), Y4.1
unnamed: R1.1, U15.16 (INT1)
unnamed: R3.1, U15.12 (INT3)

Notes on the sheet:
RF Path Switch T/R
RF Transmitter (20 Kbps)
Antenna (SMA)
D(4) = 1, D(3) = 1 For 20 Kbps BW
RF Receiver (20 Kbps)
Inertial Measurement Unit
0x18
0x68
433 MHz

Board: 4 copper layers, 236 parts (0 on the bottom side), 219 nets, no tracks yet.

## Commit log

2024-09-10 feat: first commit
    Create first commit with gitignore
2024-09-10 feat: basic project structure
2024-09-14 feat: add material list and create library dir
    Create a spreadsheet to annotate BOM and include symbols in lib/
2024-09-28 feat: add MCU, basic motor structure, sensors and power
    Initialize basic structure for the motor, sensor and power sheets.
    Update material list (mats.ods) with more components to be used.
2024-10-13 feat: add new BLDC controler and RF section
2024-11-10 feat: finish motors, RF and power monitor
2024-11-10 fix: remove library from tracked files
2024-11-11 feat: update pdf output
2024-11-12 feat: start PCB design, define board outline and basic placement
2024-11-15 feat: complete preliminar placement of PCB components
    Organize and place components for routing and export a preliminary BOM
2024-11-16 feat: add basic split power planes and redo edgecuts
    Add power plane zones and fix edgecuts constraints, also reducing the size.
2024-11-16 feat: further routing
2024-11-16 feat: reposition elements and go back to original edgecuts
    Position elements for easier routing and start from scratch.
    Revert shape design to be fully symmetrical.
2024-11-16 fix: reshape 3V3 power plane
2024-11-17 temp: commit previous to routing
